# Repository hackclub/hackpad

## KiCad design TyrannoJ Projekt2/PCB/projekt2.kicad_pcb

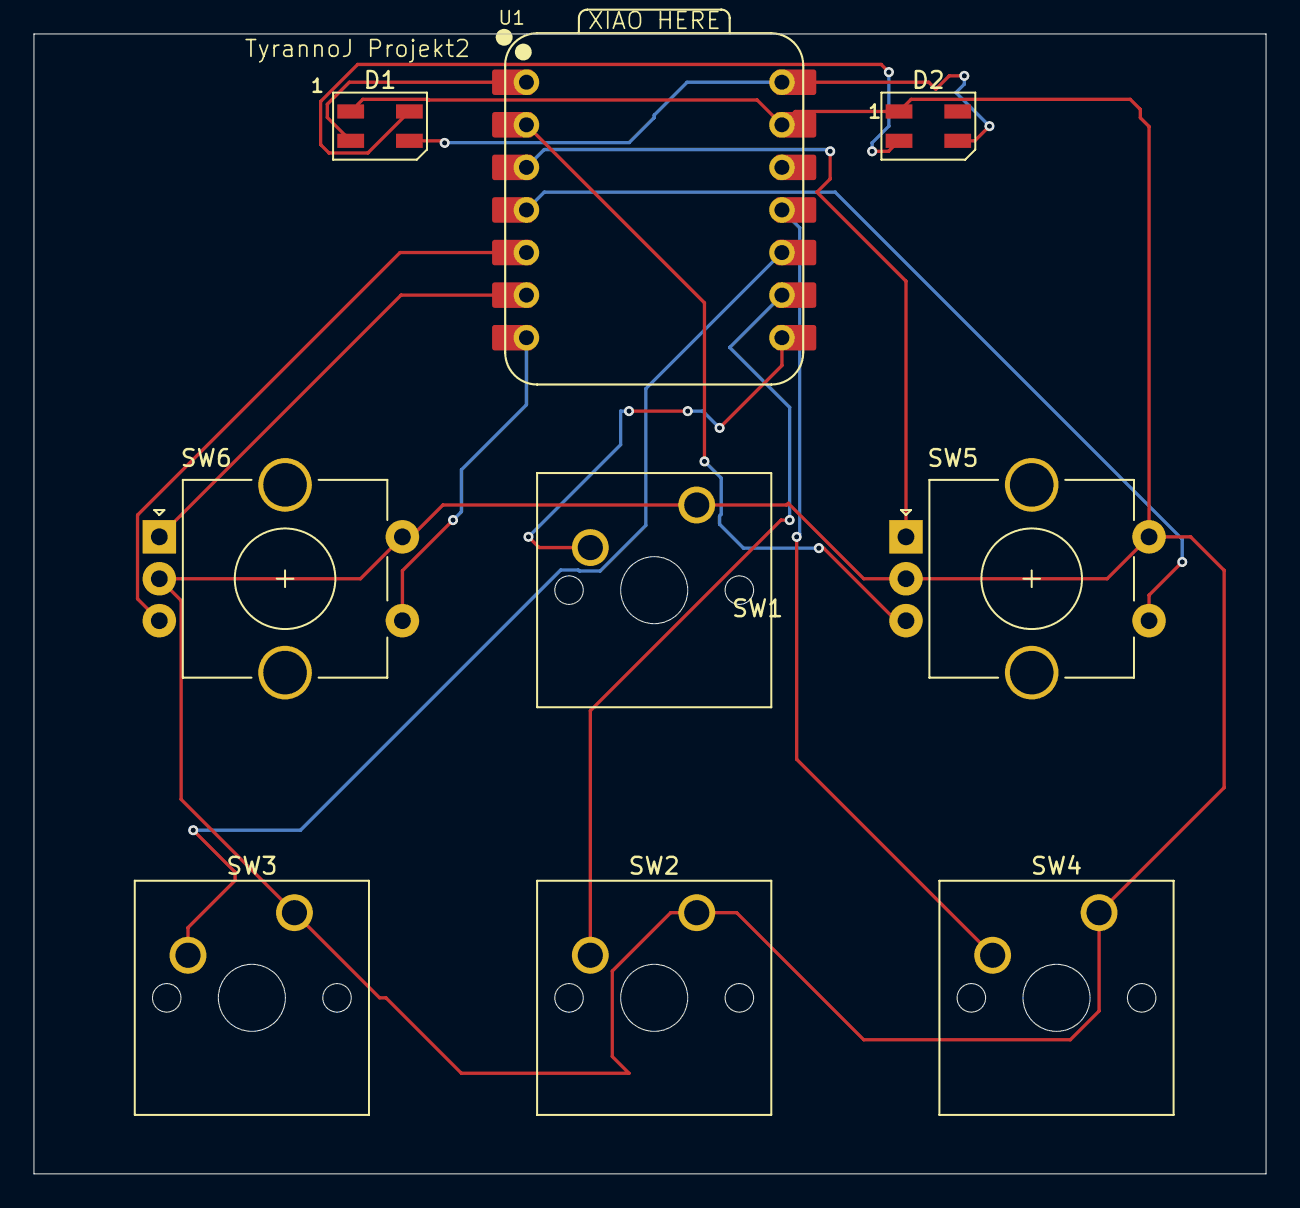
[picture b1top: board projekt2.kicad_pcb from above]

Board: 2 copper layers, 73.5 x 68.0 mm, 9 parts (0 on the bottom side), 14 nets.

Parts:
D1, D2: SK6812; LED_SK6812MINI_PLCC4_3.5x3.5mm_P1.75mm
SW1, SW2, SW3, SW4: SW_Push; SW_Cherry_MX_1.00u_PCB
SW5, SW6: RotaryEncoder_Switch; RotaryEncoder_Alps_EC11E-Switch_Vertical_H20mm_CircularMoun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
U1: XIAO-RP2040-DIP

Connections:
+5V: D1.3 (VDD), D2.3 (VDD), U1.14 (VBUS)
GND: D1.1 (VSS), D2.1 (VSS), SW1.1, SW2.1, SW3.1, SW4.1, SW5.C, SW5.S2, SW6.C, SW6.S2, U1.13 (GND)
unnamed: D1.2 (DIN), U1.1 (GPIO26/ADC0/A0)
unnamed: D1.4 (DOUT), D2.2 (DIN)
unnamed: SW6.S1, U1.7 (GPIO0/TX)
unnamed: SW1.2, U1.8 (GPIO1/RX)
unnamed: SW2.2, U1.9 (GPIO2/SCK)
unnamed: SW4.2, U1.11 (GPIO3/MOSI)
unnamed: SW3.2, U1.10 (GPIO4/MISO)
unnamed: SW6.B, U1.5 (GPIO6/SDA)
unnamed: SW6.A, U1.6 (GPIO7/SCL)
unnamed: SW5.B, U1.2 (GPIO27/ADC1/A1)
unnamed: SW5.A, U1.3 (GPIO28/ADC2/A2)
unnamed: SW5.S1, U1.4 (GPIO29/ADC3/A3)

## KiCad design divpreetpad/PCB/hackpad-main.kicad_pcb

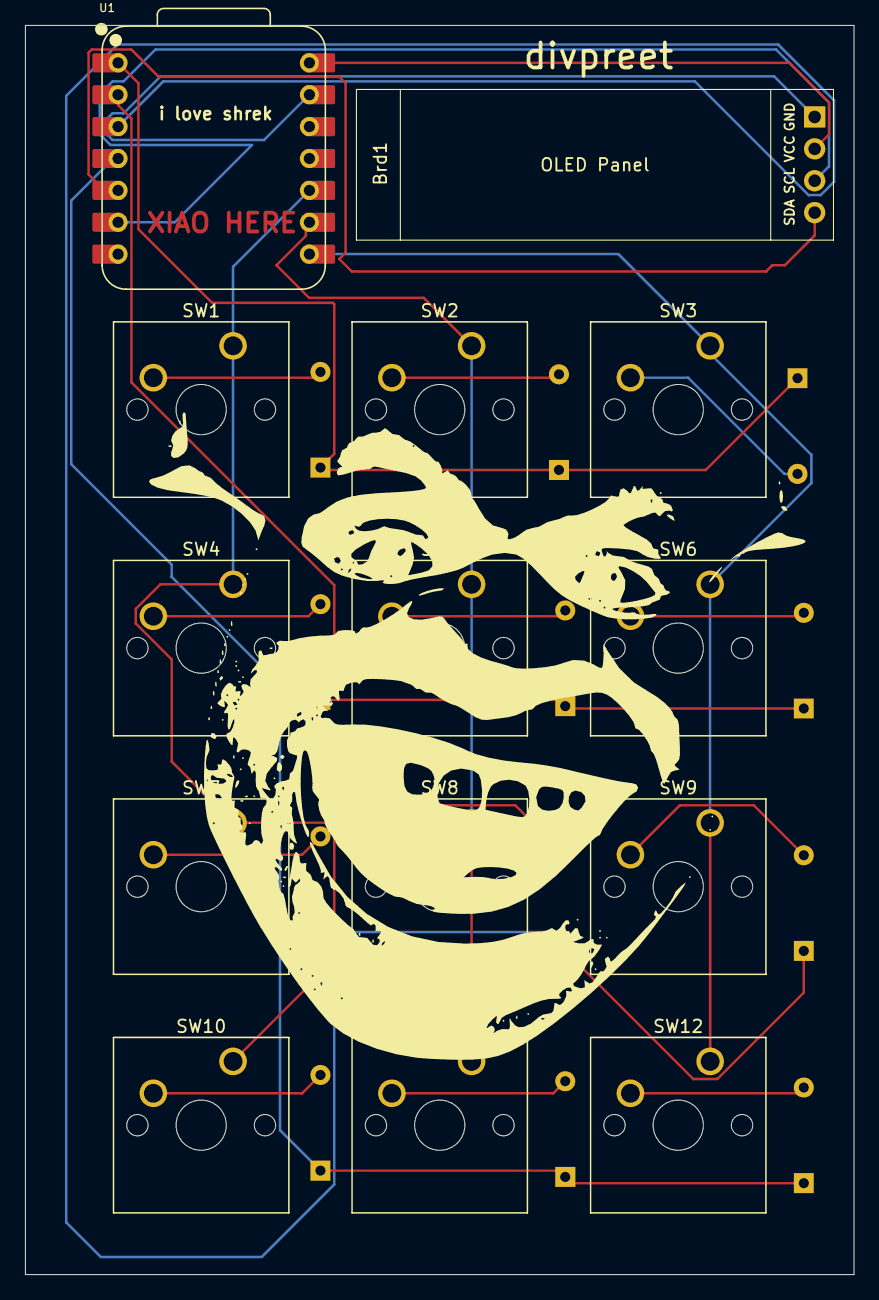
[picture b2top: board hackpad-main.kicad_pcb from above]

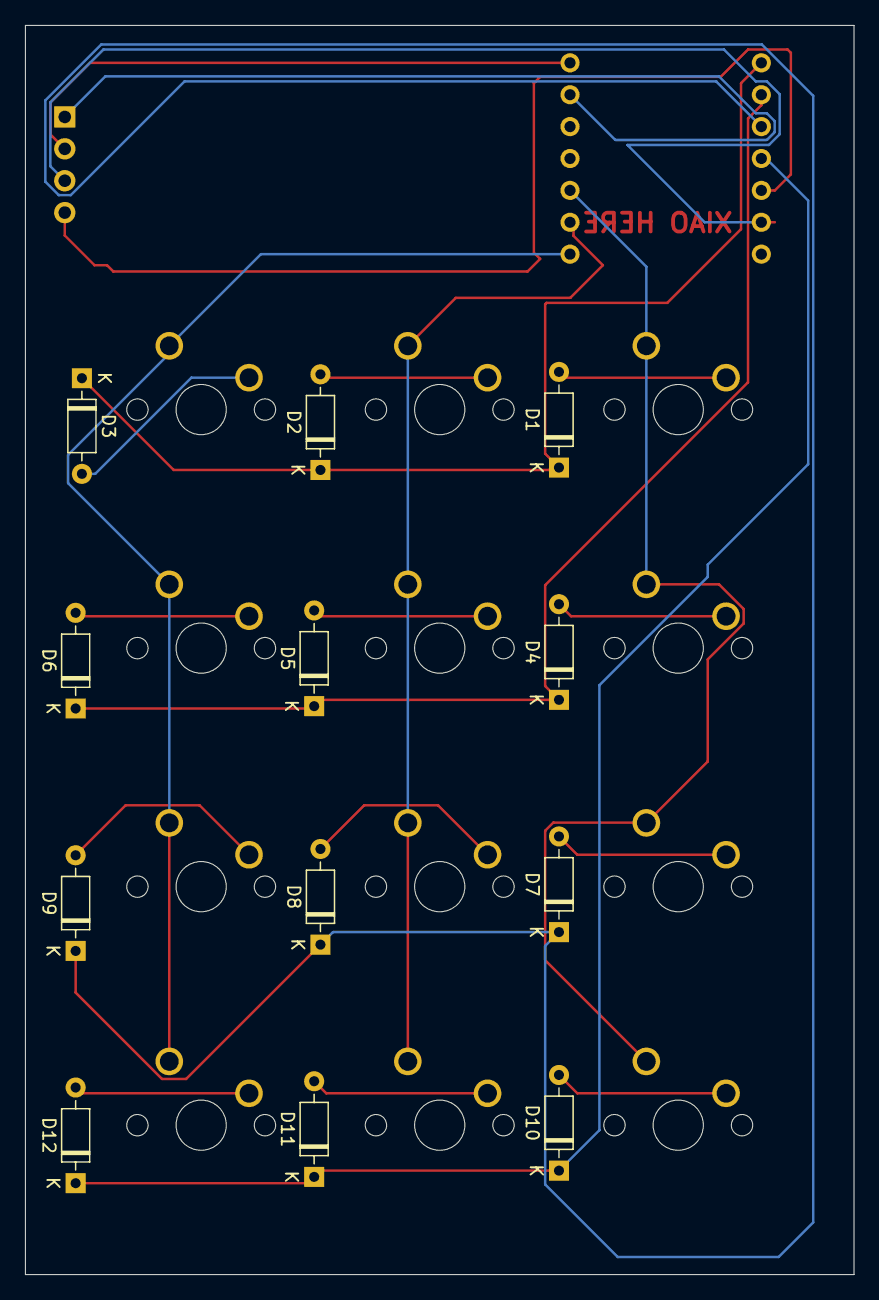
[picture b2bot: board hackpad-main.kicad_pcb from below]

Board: 2 copper layers, 66.0 x 99.5 mm, 26 parts (12 on the bottom side), 23 nets.

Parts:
Brd1: SSD1306; SSD1306-0.91-OLED-4pin-128x32
D1, D2, D3, D4, D5, D6, D7, D8, D9, D10, D11, D12: D; D_DO-35_SOD27_P7.62mm_Horizontal
SW1, SW2, SW3, SW4, SW5, SW6, SW7, SW8, SW9, SW10, SW11, SW12: SW_Push; SW_Cherry_MX_1.00u_PCB
U1: XIAO-RP2040-DIP

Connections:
+5V: Brd1.2 (VCC), U1.14 (VBUS)
GND: Brd1.1 (GND), U1.13 (GND)
unnamed: Brd1.3 (SCL), U1.6 (GPIO7/SCL)
unnamed: Brd1.4 (SDA), U1.5 (GPIO6/SDA)
unnamed: D1.2 (A), SW1.2
unnamed: D1.1 (K), D2.1 (K), D3.1 (K), U1.1 (GPIO26/ADC0/A0)
unnamed: D2.2 (A), SW2.2
unnamed: D3.2 (A), SW3.2
unnamed: D4.2 (A), SW4.2
unnamed: D4.1 (K), D5.1 (K), D6.1 (K), U1.2 (GPIO27/ADC1/A1)
unnamed: D5.2 (A), SW5.2
unnamed: D6.2 (A), SW6.2
unnamed: D7.2 (A), SW7.2
unnamed: D7.1 (K), D8.1 (K), D9.1 (K), U1.3 (GPIO28/ADC2/A2)
unnamed: D8.2 (A), SW8.2
unnamed: D9.2 (A), SW9.2
unnamed: D10.2 (A), SW10.2
unnamed: D10.1 (K), D11.1 (K), D12.1 (K), U1.4 (GPIO29/ADC3/A3)
unnamed: D11.2 (A), SW11.2
unnamed: D12.2 (A), SW12.2
unnamed: SW3.1, SW6.1, SW9.1, SW12.1, U1.8 (GPIO1/RX)
unnamed: SW2.1, SW5.1, SW8.1, SW11.1, U1.9 (GPIO2/SCK)
unnamed: SW1.1, SW4.1, SW7.1, SW10.1, U1.10 (GPIO4/MISO)

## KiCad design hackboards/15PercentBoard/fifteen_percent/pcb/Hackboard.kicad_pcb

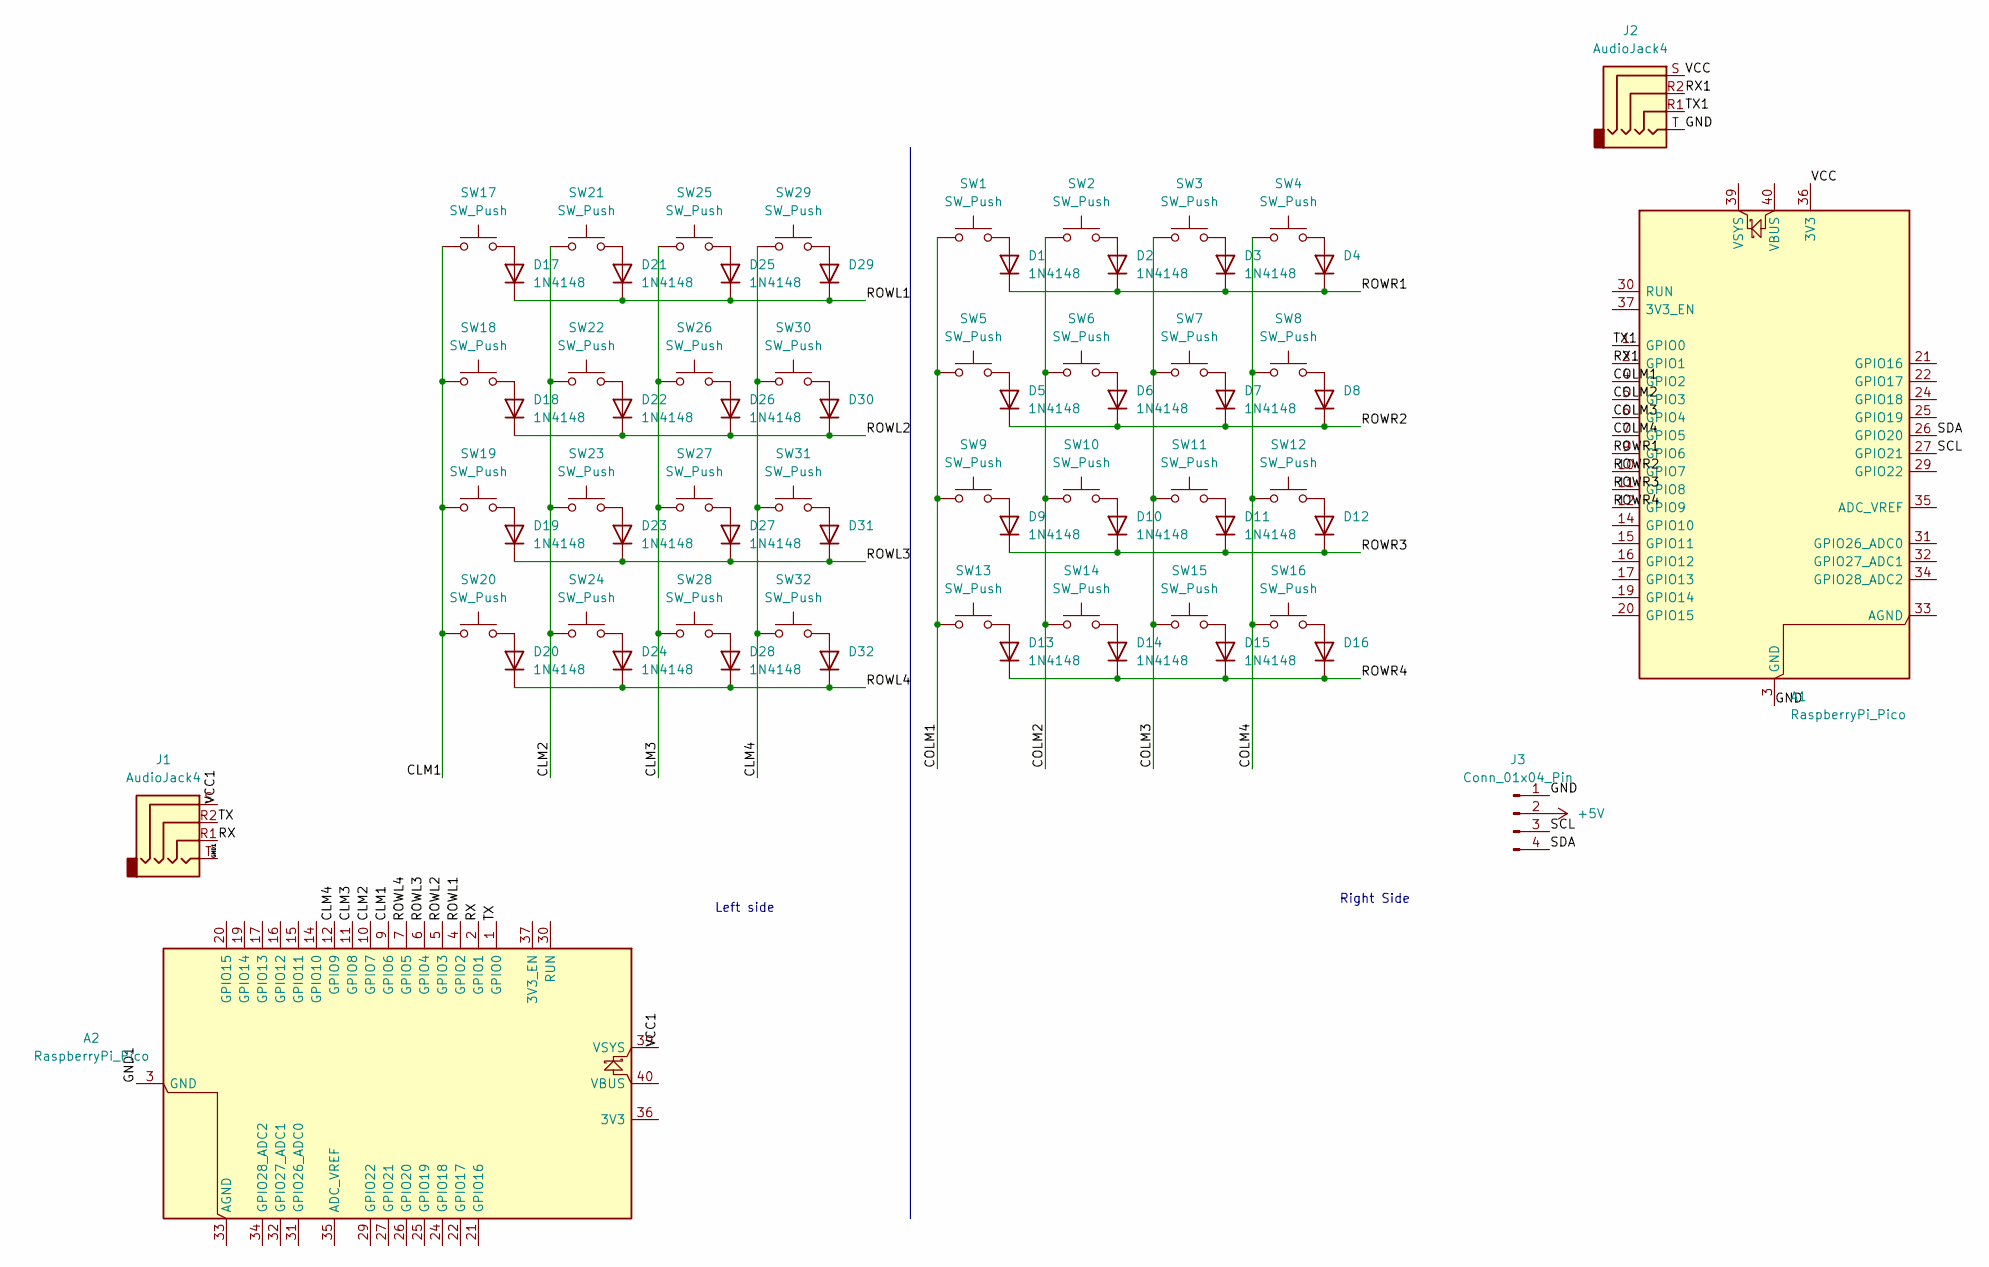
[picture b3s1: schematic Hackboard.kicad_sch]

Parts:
A1, A2: RaspberryPi_Pico; RaspberryPi_Pico_Common_Unspecified
D1, D2, D3, D4, D5, D6, D7, D8, D9, D10, D11, D12, D13, D14, D15, D16, D17, D18, D19, D20, D21, D22, D23, D24, D25, D26, D27, D28, D29, D30, D31, D32: 1N4148; D_DO-35_SOD27_P7.62mm_Horizontal
J1, J2: AudioJack4; Plug_3.5mm_CUI_SP-3541
J3: Conn_01x04_Pin; SSD1306-0.91-OLED-4pin-128x32
SW1, SW2, SW3, SW4, SW5, SW6, SW7, SW8, SW9, SW10, SW11, SW12, SW13, SW17, SW18, SW19, SW20, SW21, SW22, SW23, SW24, SW25, SW26, SW27, SW28, SW29: SW_Push; SW_Cherry_MX_1.00u_PCB
SW14, SW15, SW16, SW30, SW31, SW32: SW_Push; SW_Cherry_MX_1.50u_PCB

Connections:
+5V: J3.2
/CLM1: A2.9 (GPIO6), SW17.1, SW18.1, SW19.1, SW20.1
/CLM2: A2.10 (GPIO7), SW21.1, SW22.1, SW23.1, SW24.1
/CLM3: A2.11 (GPIO8), SW25.1, SW26.1, SW27.1, SW28.1
/CLM4: A2.12 (GPIO9), SW29.1, SW30.1, SW31.1, SW32.1
/COLM1: A1.4 (GPIO2), SW1.1, SW5.1, SW9.1, SW13.1
/COLM2: A1.5 (GPIO3), SW2.1, SW6.1, SW10.1, SW14.1
/COLM3: A1.6 (GPIO4), SW3.1, SW7.1, SW11.1, SW15.1
/COLM4: A1.7 (GPIO5), SW4.1, SW8.1, SW12.1, SW16.1
/GND: A1.3 (GND), A1.8 (GND), A1.13 (GND), A1.18 (GND), A1.23 (GND), A1.28 (GND), A1.38 (GND), J2.T, J3.1
/GND1: A2.3 (GND), A2.8 (GND), A2.13 (GND), A2.18 (GND), A2.23 (GND), A2.28 (GND), A2.38 (GND), J1.T
/ROWL1: A2.4 (GPIO2), D17.1 (K), D21.1 (K), D25.1 (K), D29.1 (K)
/ROWL2: A2.5 (GPIO3), D18.1 (K), D22.1 (K), D26.1 (K), D30.1 (K)
/ROWL3: A2.6 (GPIO4), D19.1 (K), D23.1 (K), D27.1 (K), D31.1 (K)
/ROWL4: A2.7 (GPIO5), D20.1 (K), D24.1 (K), D28.1 (K), D32.1 (K)
/ROWR1: A1.9 (GPIO6), D1.1 (K), D2.1 (K), D3.1 (K), D4.1 (K)
/ROWR2: A1.10 (GPIO7), D5.1 (K), D6.1 (K), D7.1 (K), D8.1 (K)
/ROWR3: A1.11 (GPIO8), D9.1 (K), D10.1 (K), D11.1 (K), D12.1 (K)
/ROWR4: A1.12 (GPIO9), D13.1 (K), D14.1 (K), D15.1 (K), D16.1 (K)
/RX: A2.2 (GPIO1), J1.R1
/RX1: A1.2 (GPIO1), J2.R2
/SCL: A1.27 (GPIO21), J3.3
/SDA: A1.26 (GPIO20), J3.4
/TX: A2.1 (GPIO0), J1.R2
/TX1: A1.1 (GPIO0), J2.R1
/VCC: A1.36 (3V3), J2.S
/VCC1: A2.39 (VSYS), J1.S
unnamed: D1.2 (A), SW1.2
unnamed: D2.2 (A), SW2.2
unnamed: D3.2 (A), SW3.2
unnamed: D4.2 (A), SW4.2
unnamed: D5.2 (A), SW5.2
unnamed: D6.2 (A), SW6.2
unnamed: D7.2 (A), SW7.2
unnamed: D8.2 (A), SW8.2
unnamed: D9.2 (A), SW9.2
unnamed: D10.2 (A), SW10.2
unnamed: D11.2 (A), SW11.2
unnamed: D12.2 (A), SW12.2
unnamed: D13.2 (A), SW13.2
unnamed: D14.2 (A), SW14.2
unnamed: D15.2 (A), SW15.2
unnamed: D16.2 (A), SW16.2
unnamed: D17.2 (A), SW17.2
unnamed: D18.2 (A), SW18.2
unnamed: D19.2 (A), SW19.2
unnamed: D20.2 (A), SW20.2
unnamed: D21.2 (A), SW21.2
unnamed: D22.2 (A), SW22.2
unnamed: D23.2 (A), SW23.2
unnamed: D24.2 (A), SW24.2
unnamed: D25.2 (A), SW25.2
unnamed: D26.2 (A), SW26.2
unnamed: D27.2 (A), SW27.2
unnamed: D28.2 (A), SW28.2
unnamed: D29.2 (A), SW29.2
unnamed: D30.2 (A), SW30.2
unnamed: D31.2 (A), SW31.2
unnamed: D32.2 (A), SW32.2

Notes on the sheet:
Left side
Right Side

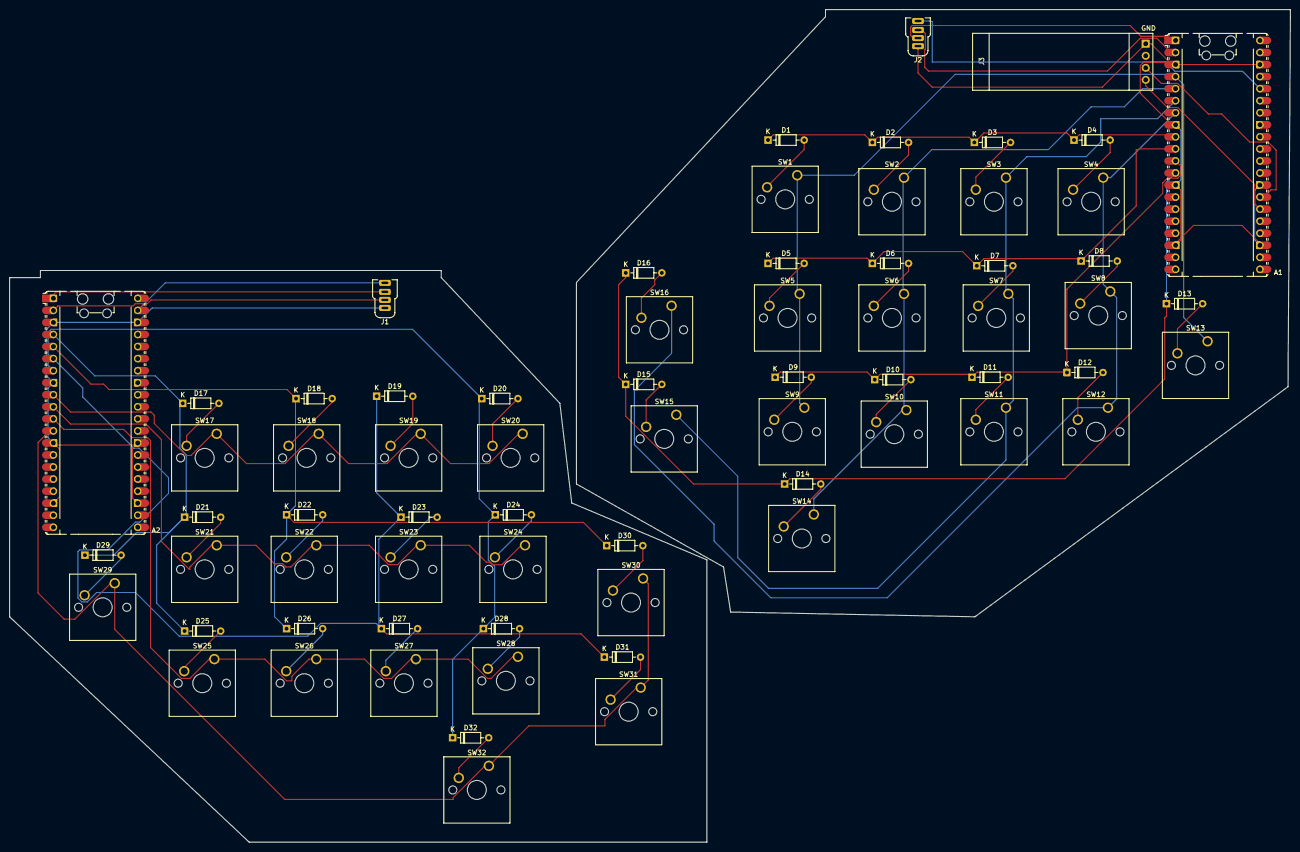
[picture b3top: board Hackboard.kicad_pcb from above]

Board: 2 copper layers, 270.0 x 175.5 mm, 69 parts (0 on the bottom side), 58 nets.
